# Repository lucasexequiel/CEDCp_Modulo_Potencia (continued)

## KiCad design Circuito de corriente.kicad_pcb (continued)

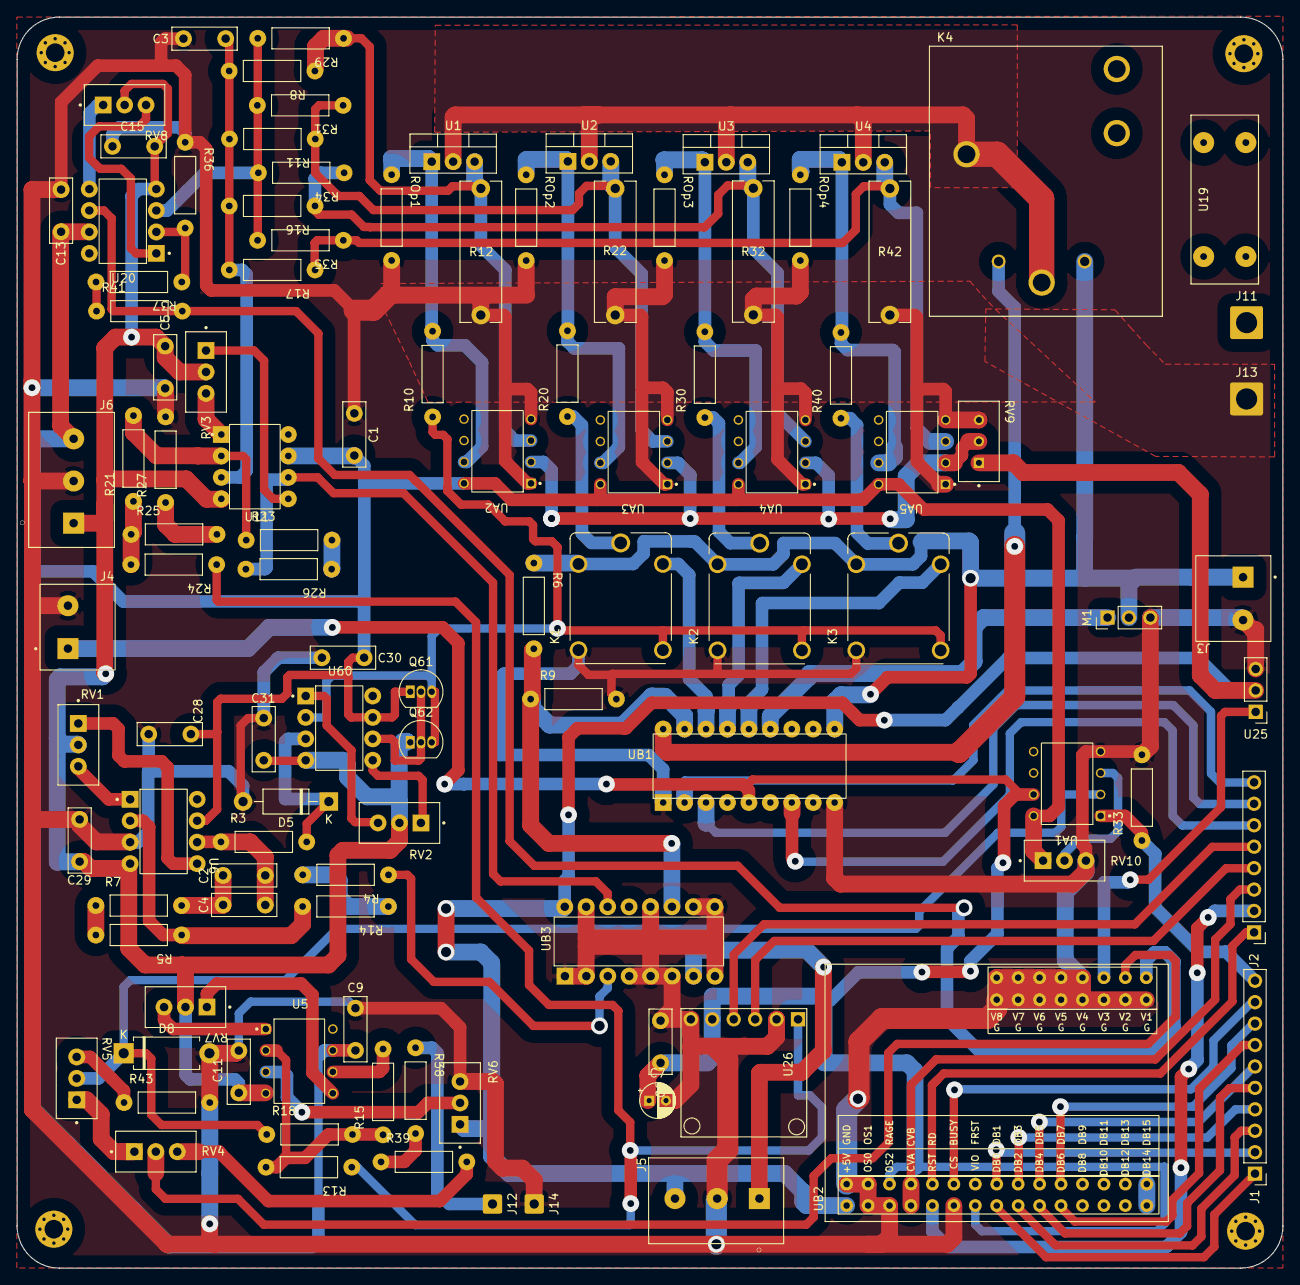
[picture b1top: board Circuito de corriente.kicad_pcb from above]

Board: 2 copper layers, 150.0 x 148.2 mm, 112 parts (0 on the bottom side), 88 nets.

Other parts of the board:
RV8: 250k; Preset_Multivueltas_Vertical

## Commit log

2022-02-05 Added Kicad files Modulo de potencia
2022-02-11 Added 3D model
2022-02-12 Gerbers files generated
2022-02-18 Reorder conection with control module
2022-02-28 Gerbers generated again
2022-03-06 Version V1 (Clearence + pads)
2022-03-15 Origin added
2022-03-21 Heat sink added + Large pads
2022-04-16 Pads mas grandes y correccion de vias
2022-04-20 Se agrandaron los pads de las VIAS y ensancharon las pistas
2022-05-04 V4 Ltspice
2022-05-04 VF4 actualizaciones
